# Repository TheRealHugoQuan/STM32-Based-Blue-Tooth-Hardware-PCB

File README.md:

# 📡 STM32 Bluetooth Low Energy (BLE) Node

## 📖 Overview
This repository contains the complete hardware design files (schematic and PCB layout) for a custom Bluetooth Low Energy (BLE) development board powered by the STM32 architecture. 

Designed specifically for [e.g., low-power IoT applications / wearable prototyping], this board integrates a high-performance ARM Cortex-M core with a 2.4GHz RF radio, optimized power routing, and exposed peripheral headers for rapid sensor integration.

## 🛠️ Hardware Specifications
* **Microcontroller:** [e.g., STM32WB55RG / STM32F4 + External NRF module]
* **Wireless Protocol:** Bluetooth Low Energy (BLE) [e.g., 5.2]
* **Antenna Design:** [e.g., 2.4GHz Meandering PCB Trace Antenna / U.FL connector for external antenna]
* **Clock/Oscillators:** * High-Speed External (HSE): [e.g., 32 MHz crystal for RF timing]
  * Low-Speed External (LSE): [e.g., 32.768 kHz crystal for RTC/Low Power modes]
* **Power Supply:** [e.g., 3.3V LDO regulated from a 5V USB-C input or single Li-Po cell]
* **Programming Interface:** Standard 10-pin SWD (Serial Wire Debug) header
* **Dimensions:** [e.g., 40mm x 25mm]
* **Layers:** [e.g., 4-Layer FR4 with dedicated continuous ground plane for RF shielding]

## 📁 Repository Structure
* `/hardware/` - Core KiCad project files (`.kicad_pro`, `.kicad_sch`, `.kicad_pcb`).
* `/fabrication/` - Exported Gerber files, drill files, and BOM/CPL files ready for PCB assembly (PCBA).
* `/firmware/` - Placeholder or link to the accompanying STM32CubeIDE / Zephyr RTOS software repository.
* `/datasheets/` - Critical component datasheets (MCU, Antenna matching components).

## 🚀 Getting Started
To view or

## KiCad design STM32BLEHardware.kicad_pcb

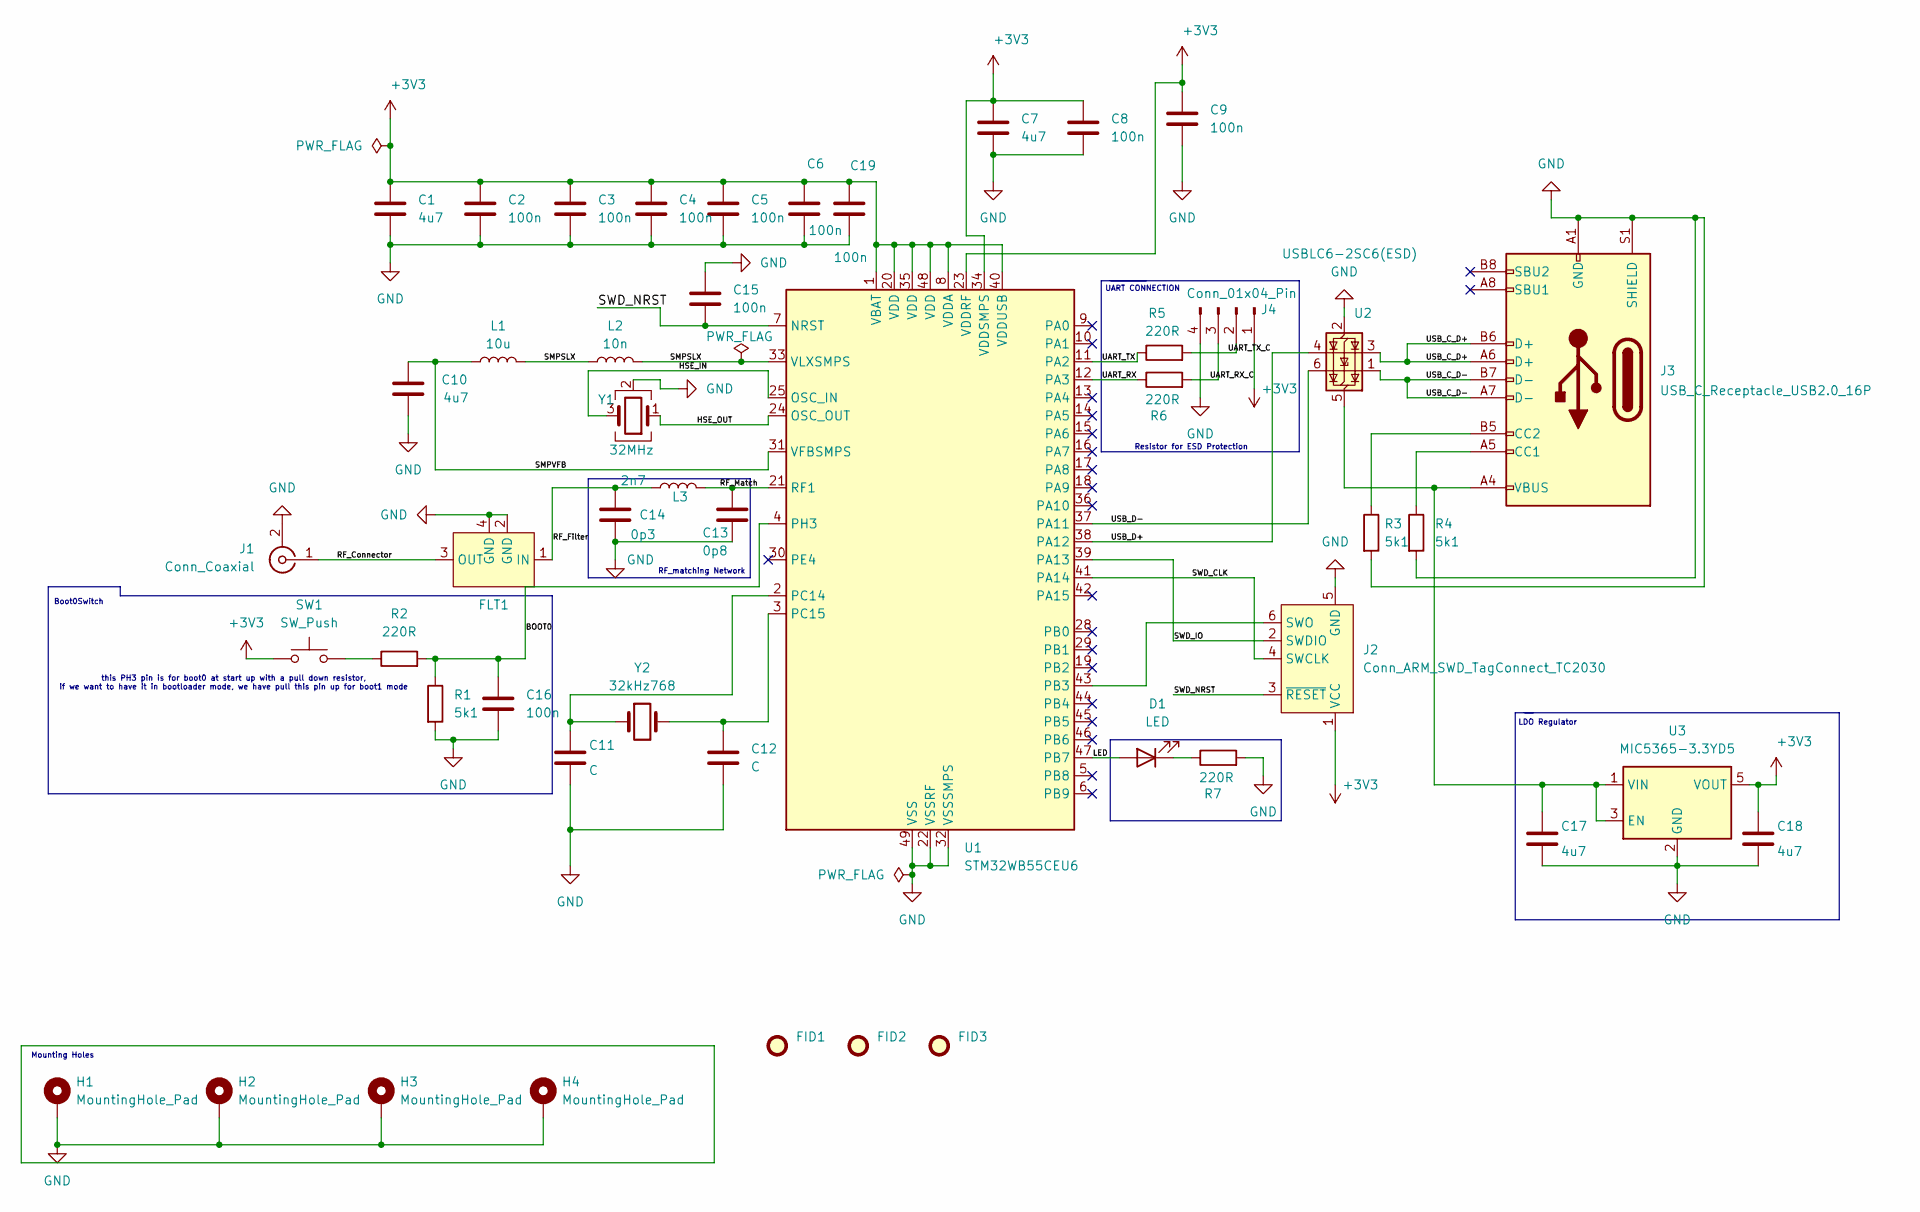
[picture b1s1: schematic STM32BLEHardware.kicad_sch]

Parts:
C1, C7, C10, C17, C18: 4u7; C_0603_1608Metric; Manufacturer Part No. 0603ZD475KAT2A
C2, C3, C4, C5, C6, C8, C9, C15, C16, C19: 100n; C_0402_1005Metric; Manufacturer Part No. VX 0402ZC104KAT2A
C11, C12: C; C_0402_1005Metric; Manufacturer Part No. 04025A120JAT2A
C13: 0p8; C_0402_1005Metric; Manufacturer Part No. GJM1555C1HR80WB01D
C14: 0p3; C_0402_1005Metric; Manufacturer Part No. GJM1555C1HR30WB01D
D1: LED; LED_0402_1005Metric; Manufacturer Part No. 150040GS73220
FID1, FID2, FID3: Fiducial; Fiducial_1mm_Mask2mm
FLT1: DLF162500LT-5028A1; Untitled; Manufacturer Part No. DLF162500LT-5028A1
H1, H2, H3, H4: MountingHole_Pad; MountingHole_2.2mm_M2_Pad_Via
J1: Conn_Coaxial; U.FL_Hirose_U.FL-R-SMT-1_Vertical; Manufacturer Part No. U.FL-R-SMT-1(10)
J2: Conn_ARM_SWD_TagConnect_TC2030; Tag-Connect_TC2030-IDC-FP_2x03_P1.27mm_Vertical; Manufacturer Part No. TC2030-IDC-NL (Cable)
J3: USB_C_Receptacle_USB2.0_16P; USB_C_Receptacle_GCT_USB4105-xx-A_16P_TopMnt_Horizontal; Manufacturer Part No. USB4105-GF-A
J4: Conn_01x04_Pin; Molex_PicoBlade_53048-0410_1x04_P1.25mm_Horizontal; Manufacturer Part No. 53048-0410
L1: 10u; L_0805_2012Metric; Manufacturer Part No. LQM21PN100MGR
L2: 10n; L_0402_1005Metric; Manufacturer Part No. LQG15HS10NJ02D
L3: 2n7; L_0402_1005Metric; Manufacturer Part No. LQG15HS2N7S02D
R1, R3, R4: 5k1; R_0402_1005Metric; Manufacturer Part No. RC0402JR-075K1L
R2, R5, R6, R7: 220R; R_0402_1005Metric; Manufacturer Part No. RC0402JR-07220RL
SW1: SW_Push; SW_SPST_CK_RS282G05A3; Manufacturer Part No. RS-282G05A3-SM RT
U1: STM32WB55CEU6; QFN-48-1EP_7x7mm_P0.5mm_EP5.6x5.6mm; Manufacturer Part No. STM32WB55CEU6
U2: USBLC6-2SC6(ESD); SOT-23-6; Manufacturer Part No. USBLC6-2SC6
U3: MIC5365-3.3YD5; TSOT-23-5; Manufacturer Part No. MIC5365-3.3YD5-TR
Y1: 32MHz; Crystal_SMD_2016-4Pin_2.0x1.6mm; Manufacturer Part No. NX2016SA-32M-EXS00A-CS06465
Y2: 32kHz768; Crystal_SMD_2012-2Pin_2.0x1.2mm; Manufacturer Part No. NX2012SA-32.768K-STD-MUB-1

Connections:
+3V3: C1.1, C2.1, C3.1, C4.1, C5.1, C6.1, C7.1, C8.1, C9.1, C18.1, C19.1, J2.1 (VCC), J4.1, SW1.1, U1.1 (VBAT), U1.8 (VDDA), U1.20 (VDD), U1.23 (VDDRF), U1.34 (VDDSMPS), U1.35 (VDD), U1.40 (VDDUSB), U1.48 (VDD), U3.5 (VOUT)
/BOOT0: C16.1, R1.1, R2.2, U1.4 (PH3)
/HSE_IN: U1.25 (OSC_IN), Y1.3
/HSE_OUT: U1.24 (OSC_OUT), Y1.1
/LED: D1.2 (A), U1.47 (PB7)
/RF_Connector: FLT1.3 (OUT), J1.1 (In)
/RF_Filter: C14.1, FLT1.1 (IN), L3.1
/RF_Match: C13.1, L3.2, U1.21 (RF1)
/SMPSLX: L1.2, L2.1, L2.2, U1.33 (VLXSMPS)
/SMPVFB: C10.1, L1.1, U1.31 (VFBSMPS)
/SWD_CLK: J2.4 (SWCLK), U1.41 (PA14)
/SWD_IO: J2.2 (SWDIO), U1.39 (PA13)
/SWD_NRST: C15.2, J2.3 (~RESET), U1.7 (NRST)
/UART_RX: R6.1, U1.12 (PA3)
/UART_RX_C: J4.3, R6.2
/UART_TX: R5.1, U1.11 (PA2)
/UART_TX_C: J4.2, R5.2
/USB_C_D+: J3.A6 (D+), J3.B6 (D+), U2.3 (I/O2)
/USB_C_D-: J3.A7 (D-), J3.B7 (D-), U2.1 (I/O1)
/USB_D+: U1.38 (PA12), U2.4 (I/O2)
/USB_D-: U1.37 (PA11), U2.6 (I/O1)
GND: C1.2, C2.2, C3.2, C4.2, C5.2, C6.2, C7.2, C8.2, C9.2, C10.2, C11.2, C12.2, C13.2, C14.2, C15.1, C16.2, C17.2, C18.2, C19.2, FLT1.2 (GND), FLT1.4 (GND), H1.1, H2.1, H3.1, H4.1, J1.2 (Ext), J2.5 (GND), J3.A1 (GND), J3.A12 (GND), J3.B1 (GND), J3.B12 (GND), J3.S1 (SHIELD), J4.4, R1.2, R3.2, R4.2, R7.2, U1.22 (VSSRF), U1.32 (VSSSMPS), U1.49 (VSS), U2.2 (GND), U3.2 (GND), Y1.2 (G), Y1.4 (G)
unnamed: D1.1 (K), R7.1
unnamed: J2.6 (SWO), U1.43 (PB3)
unnamed: J3.A5 (CC1), R4.1
unnamed: J3.B5 (CC2), R3.1
unnamed: R2.1, SW1.2
unnamed: C11.1, U1.2 (PC14), Y2.1
unnamed: C12.1, U1.3 (PC15), Y2.2
unnamed: C17.1, J3.A4 (VBUS), J3.A9 (VBUS), J3.B4 (VBUS), J3.B9 (VBUS), U2.5 (VBUS), U3.1 (VIN), U3.3 (EN)

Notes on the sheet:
UART CONNECTION
LDO Regulator
Resistor for ESD Protection
Boot0Switch
RF_matching Network
this PH3 pin is for boot0 at start up with a pull down resistor, if we want to have it in bootloader mode, we have pull this pin up for boot1 mode
Mounting Holes

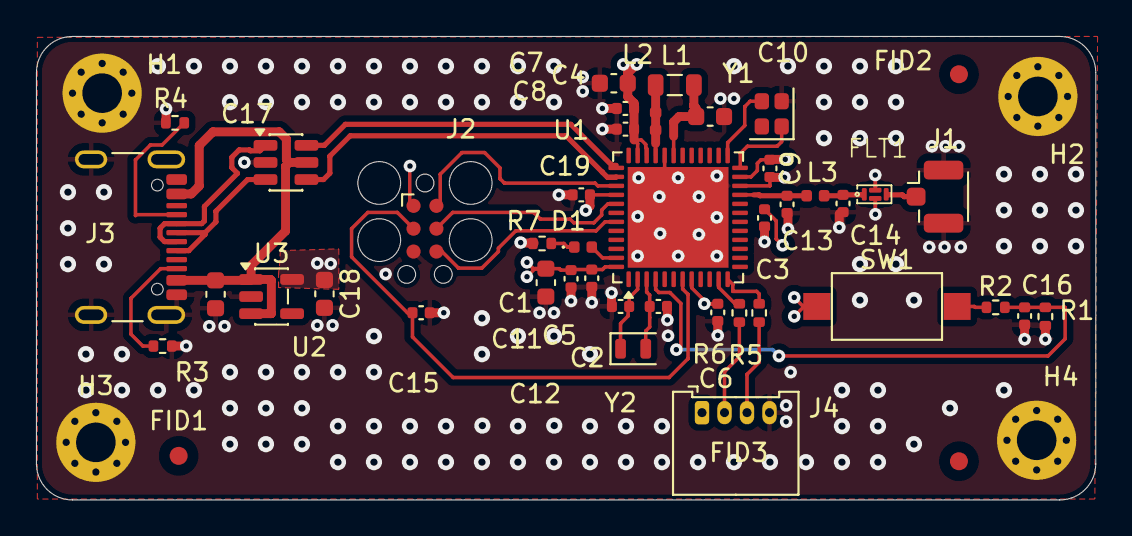
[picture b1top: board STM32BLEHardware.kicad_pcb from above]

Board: 4 copper layers, 58.8 x 25.8 mm, 48 parts (0 on the bottom side), 30 nets.

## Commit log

2026-03-08 first revision files
2026-03-08 Initialize README with project details and specifications
    Added detailed overview, hardware specifications, and repository structure for the STM32 BLE Node project.
2026-03-08 Remove schematic and board layout section
    Removed schematic and board layout section from README.
